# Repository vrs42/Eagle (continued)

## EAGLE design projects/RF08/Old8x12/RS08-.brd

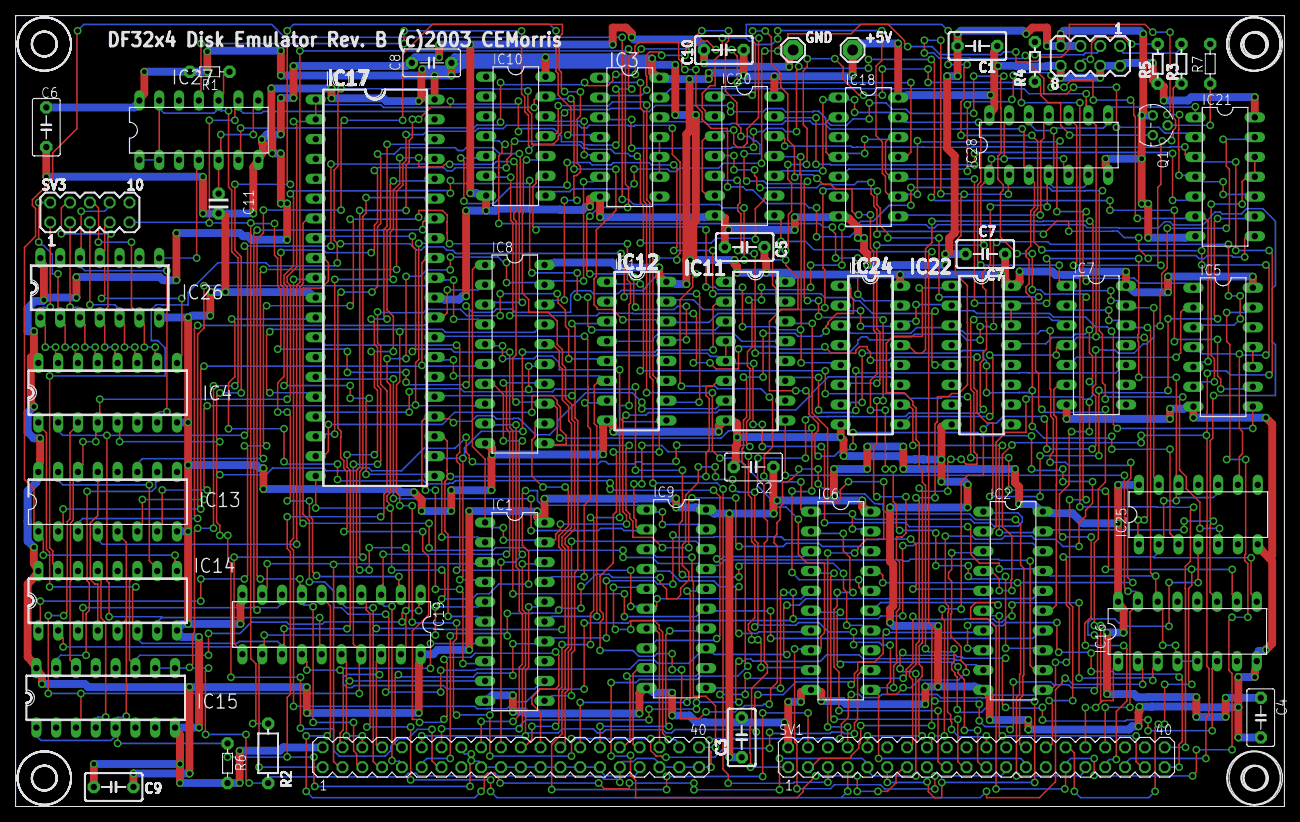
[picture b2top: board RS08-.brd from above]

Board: 2 copper layers, 162.7 x 101.4 mm, 56 parts (0 on the bottom side), 153 nets.

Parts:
+5V: SE14
C1, C2, C3, C4, C5, C6, C7, C8, C9, C10: C5B3.5
C11: C-2,5
GND: SE14
IC1, IC8, IC9, IC19: 74LS240N; DIL20
IC2, IC6: 74LS244N; DIL20
IC3: 74LS00N; DIL14
IC4: 74LS138N; DIL16
IC5: 74LS32N; DIL14
IC7, IC18, IC25: 74LS74N; DIL14
IC10: 74LS04N; DIL14
IC11, IC12, IC13, IC14, IC15, IC16: 74LS191N; DIL16
IC17: DS1258; DIL40
IC20: 74LS02N; DIL14
IC21: 74LS01N; DIL14
IC22, IC24: 74LS155N; DIL16
IC26: 74LS30N; DIL14
IC27: 74LS86N; DIL14
IC28: 74LS07N; DIL14
Q1: 2N3904; TO92
R1: 1K; R-5
R2: 1K; R-7,5
R3, R4, R5: 220; R-5
R6: 0; R-5
R7: 4.7K; R-5
SV1: BUS1; MA20-2
SV2: BUS2; MA20-2
SV3: WRLOCK; MA05-2
SV4: PANEL LEDS; MA04-2
U$1, U$2, U$3, U$4: 3,0

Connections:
0V: IC2.17, IC7.2, IC7.12, IC11.4, IC11.5, IC12.5, IC13.5, IC14.5, IC15.1, IC15.5, IC16.4, IC16.5, IC16.14, R6.1, SV2.16, SV2.17, SV2.19, SV2.21, SV2.23, SV2.25, SV2.27, SV2.29, SV2.33
!660-663: IC5.8, IC22.2, IC24.2, IC24.14
!(NED+EWL): IC2.13, IC20.1
!ACBUS0: IC2.3, IC8.12, SV2.11
!ACBUS1: IC8.14, IC19.3, SV2.9
!ACBUS2: IC8.16, IC19.5, SV2.7
!ACBUS3: IC8.18, IC19.7, SV2.5
!ACBUS4: IC1.3, IC19.9, SV2.3
!ACBUS5: IC1.5, IC19.12, SV2.1
!ACBUS6: IC1.7, IC19.14, SV2.4
!ACBUS7: IC1.9, IC19.16, SV2.6
!ACBUS8: IC1.12, IC19.18, SV2.8
!ACBUS9: IC1.14, IC2.5, SV2.10
!ACBUS10: IC1.16, IC2.7, SV2.12
!ACBUS11: IC1.18, IC2.9, SV2.14
!ACCLEAR: IC21.1, IC28.4, IC28.6, IC28.8, IC28.12, SV1.1
!BADDAC: IC7.3, SV1.10
!BBREAK: IC4.4, IC10.13, IC11.14, IC12.14, IC13.14, IC14.14, IC15.14, IC17.1, IC17.2, SV1.8
!BRK_RQ: IC7.8, SV2.15
!BWCO: IC7.11, IC18.3, SV1.12
!DATA0: IC8.9, SV2.18
!DATA1: IC8.7, SV2.20
!DATA2: IC8.5, SV2.22
!DATA3: IC8.3, SV2.24
!DATA4: IC9.18, SV2.26
!DATA5: IC9.16, SV2.28
!DATA6: IC9.14, SV2.30
!DATA7: IC9.12, SV2.32
!DATA8: IC9.9, SV2.34
!DATA9: IC9.7, SV2.36
!DATA10: IC9.5, SV2.38
!DATA11: IC9.3, SV2.40
!DRL: IC2.15, IC7.6
!EA: IC10.10, SV1.4
!EWL: IC18.8, IC28.11
!INT_RQ: IC21.13, SV1.16
!IOP4: IC10.4, IC24.15
!IOS: IC21.4, IC21.10, IC28.2, SV1.14
!IOT601: IC22.7, IC27.12
!IOT602: IC3.12, IC24.7, IC25.3, IC28.3
!IOT604: IC3.13, IC7.4, IC24.9, IC25.1, IC28.9
!IOT612: IC24.6, IC28.1, IC28.5, IC28.13
!IOT614: IC2.19, IC14.11, IC15.11, IC16.11, IC19.1, IC19.19, IC24.10
!IOT621: IC10.5, IC22.5
!IOT622: IC10.9, IC20.11, IC24.5
!IOT624: IC1.1, IC1.19, IC8.1, IC24.11
!LAD: IC3.8, IC7.10, IC11.11, IC12.11, IC13.11
!OE: IC3.6, IC8.19, IC9.1, IC9.19, IC17.20
!SCL: IC7.1, IC7.13, IC18.1, IC18.13, IC20.10, IC25.13
!WE: IC2.1, IC6.1, IC6.19, IC17.39, IC27.9, R2.2, SV3.9
!WR1: IC4.15, IC26.1, SV3.1
!WR2: IC4.14, IC26.2, SV3.2
!WR3: IC4.13, IC26.3, SV3.3
!WR4: IC4.12, IC26.4, SV3.4
!WR5: IC4.11, IC26.5, SV3.5
!WR6: IC4.10, IC26.6, SV3.6
!WR7: IC4.9, IC26.11, SV3.7
!WR8: IC4.7, IC26.12, SV3.8
BAC0: IC13.9, SV1.18
BAC1: IC13.10, IC15.15, SV1.20
BAC2: IC13.1, IC14.9, SV1.22
BAC3: IC13.15, IC14.10, SV1.24
BAC4: IC12.9, IC14.1, SV1.26
BAC5: IC12.10, IC14.15, SV1.28
BAC6: IC12.1, IC16.10, SV1.30
BAC7: IC12.15, IC16.1, SV1.32
BAC8: IC11.9, IC16.15, SV1.34
BAC9: IC11.10, SV1.36
BAC10: IC11.1, SV1.38
BAC11: IC11.15, SV1.40
BIOP1: IC22.1, SV1.11
BIOP2: IC24.1, SV1.13
BIOP4: IC10.3, SV1.15
BMB0: IC6.2, SV1.17
BMB1: IC6.4, SV1.19
BMB2: IC6.6, SV1.21
BMB3: IC3.1, IC6.8, SV1.23
BMB4: IC3.2, IC6.11, SV1.25
BMB5: IC5.12, IC6.13, SV1.27
BMB6: IC5.13, IC6.15, SV1.29
BMB7: IC6.17, IC22.3, IC24.3, SV1.31
BMB8: IC2.2, IC22.13, IC24.13, SV1.33
BMB9: IC2.4, IC20.12, IC21.3, SV1.35
BMB10: IC2.6, SV1.37
BMB11: IC2.8, SV1.39
BRK_RQ: IC7.9, R7.2
BTS3: IC4.6, SV1.6
DATA_IN: IC3.4, IC4.5, IC25.5, SV2.13
DISK_LED: R4.1, SV4.3
DMA0: IC8.8, IC13.7, IC17.33
DMA1: IC8.6, IC13.6, IC17.32
DMA2: IC8.4, IC13.2, IC17.31
DMA3: IC8.2, IC13.3, IC17.29
DMA4: IC1.17, IC12.7, IC17.28
DMA5: IC1.15, IC12.6, IC17.27
DMA6: IC1.13, IC12.2, IC17.26
DMA7: IC1.11, IC12.3, IC17.25
DMA8: IC1.8, IC11.7, IC17.24
DMA9: IC1.6, IC11.6, IC17.23
DMA10: IC1.4, IC11.2, IC17.22
DMA11: IC1.2, IC11.3, IC17.21
DQ0: IC6.18, IC8.11, IC17.19
DQ1: IC6.16, IC8.13, IC17.18
DQ2: IC6.14, IC8.15, IC17.17
DQ3: IC6.12, IC8.17, IC17.16
DQ4: IC6.9, IC9.2, IC17.15
DQ5: IC6.7, IC9.4, IC17.14
DQ6: IC6.5, IC9.6, IC17.13
DQ7: IC6.3, IC9.8, IC17.12
DQ8: IC2.18, IC9.11, IC17.10
DQ9: IC2.16, IC9.13, IC17.9
DQ10: IC2.14, IC9.15, IC17.8
DQ11: IC2.12, IC9.17, IC17.7
DRL: IC5.2, IC7.5
EA1: IC10.11, IC16.3, IC19.2, SV1.5
EA2: IC16.2, IC19.4, SV1.7
EA3: IC16.6, IC19.6, SV1.9
EMA1: IC14.3, IC17.34, IC19.8
EMA2: IC14.2, IC17.35, IC19.11
EMA3: IC4.1, IC14.6, IC17.36, IC19.13
EMA4: IC4.2, IC14.7, IC17.37, IC19.15
EMA5: IC4.3, IC15.3, IC17.38, IC19.17
EWL: IC5.1, IC18.9, IC20.2
EWLSET: IC18.11, IC27.6
GND: C1.2, C2.2, C3.2, C4.2, C5.2, C6.2, C7.2, C8.2, C9.2, C10.2, C11.2, GND.MP, IC1.10, IC2.10, IC3.7, IC4.8, IC5.7, IC6.10, IC7.7, IC8.10, IC9.10, IC10.7, IC11.8, IC12.8, IC13.8, IC14.8, IC15.8, IC16.8, IC17.11, IC17.30, IC18.7, IC19.10, IC20.7, IC21.7, IC22.8, IC24.8, IC25.7, IC26.7, IC27.7, IC28.7, Q1.3, R6.2, SV1.2, SV2.2, SV4.5, SV4.7
IOT601: IC20.9, IC27.11
IOT621: IC10.6, IC21.9
LAD: IC3.9, IC3.10, IC3.11
unnamed: C11.1, IC27.5, IC27.8
unnamed: IC5.6, IC21.11, IC21.12
unnamed: IC28.10, R3.2
unnamed: IC3.5, IC10.12
unnamed: Q1.1, R4.2
unnamed: R5.2, SV4.6
unnamed: IC13.13, IC14.4
unnamed: IC12.13, IC13.4
unnamed: IC11.13, IC12.4
unnamed: IC3.3, IC5.9
unnamed: IC14.13, IC15.4
unnamed: IC5.10, IC5.11
unnamed: IC20.13, IC21.5
unnamed: IC5.3, IC20.5
unnamed: IC10.8, IC21.2
unnamed: IC26.8, IC27.4
unnamed: Q1.2, R7.1
NED: IC5.4, IC20.3, IC20.6, IC25.9
NEDSET: IC15.2, IC25.11
NOERR: IC20.4, IC21.8
PWRCLR: IC20.8, IC25.4, SV1.3
TRC: IC5.5, IC18.5, IC21.6
V+: IC2.11, IC15.9, IC15.10, IC16.9, IC18.2, IC18.4, IC18.10, IC18.12, IC22.14, IC22.15, IC25.2, IC25.10, IC25.12, IC27.1, IC27.2, IC27.10, IC27.13, R1.1, R2.1, SV2.31, SV2.35, SV2.37, SV2.39
VCC: +5V.MP, C1.1, C2.1, C3.1, C4.1, C5.1, C6.1, C7.1, C8.1, C9.1, C10.1, IC1.20, IC2.20, IC3.14, IC4.16, IC5.14, IC6.20, IC7.14, IC8.20, IC9.20, IC10.14, IC11.16, IC12.16, IC13.16, IC14.16, IC15.16, IC16.16, IC17.40, IC18.14, IC19.20, IC20.14, IC21.14, IC22.16, IC24.16, IC25.14, IC26.14, IC27.14, IC28.14, R1.2, R5.1, SV4.2, SV4.4, SV4.8
WRITELOCK_LED: R3.1, SV4.1

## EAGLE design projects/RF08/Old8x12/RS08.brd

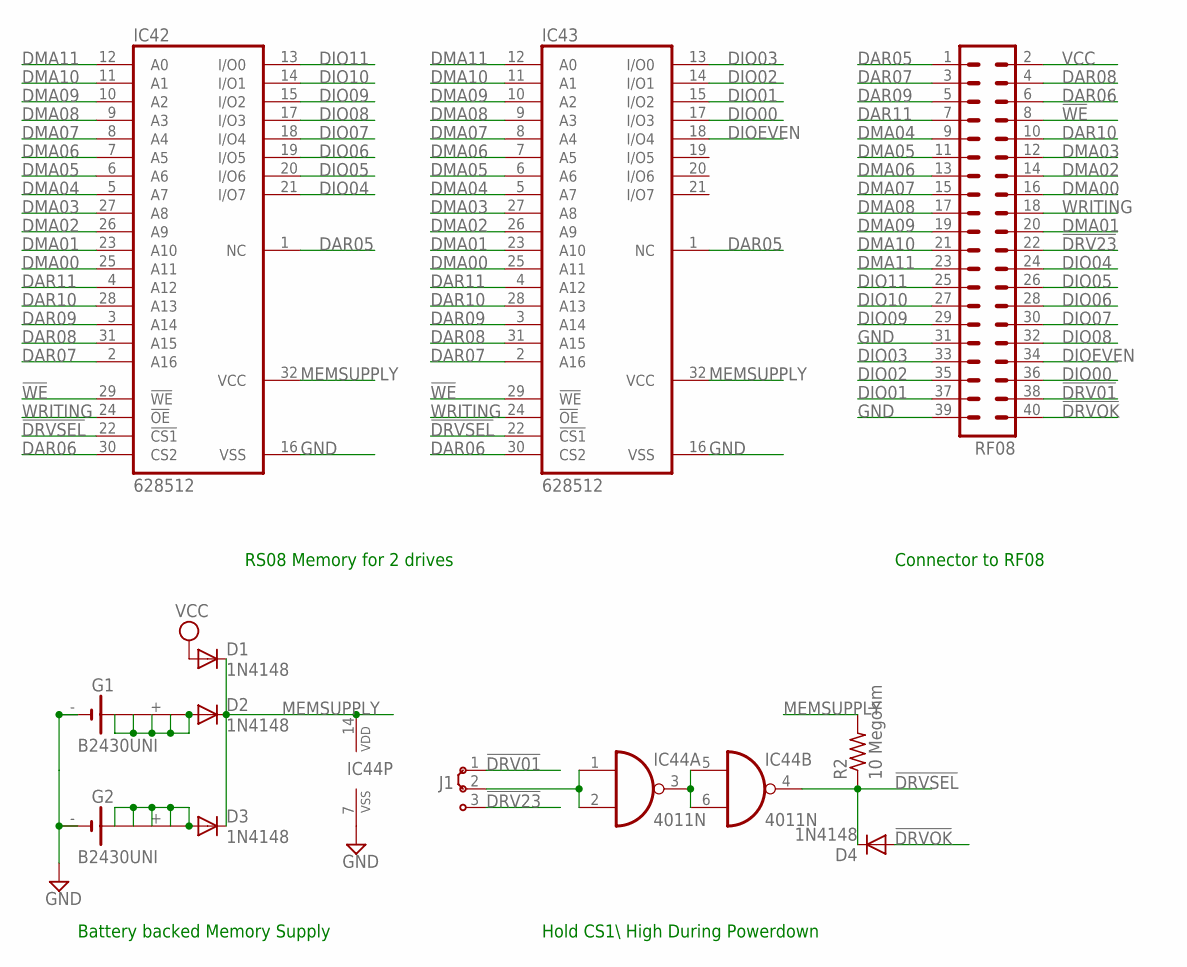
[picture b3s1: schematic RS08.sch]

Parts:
D1, D2, D3, D4: 1N4148; DO35-10
G1, G2: B2430UNI
IC42, IC43: 628512; DIL32
IC44: 4011N; DIL14
J1: J2X2MM; 04C
R2: 10 Megohm; 0207/10
RF08: MA20-2

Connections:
!DRV01: J1.1, RF08.38
!DRV23: J1.3, RF08.22
!DRVOK: D4.A, RF08.40
!DRVSEL: D4.C, IC42.22 (!CS1), IC43.22 (!CS1), IC44.4 (O), R2.1
!WE: IC42.29 (!WE), IC43.29 (!WE), RF08.8
DAR05: IC42.1 (NC), IC43.1 (NC), RF08.1
DAR06: IC42.30 (CS2), IC43.30 (CS2), RF08.6
DAR07: IC42.2 (A16), IC43.2 (A16), RF08.3
DAR08: IC42.31 (A15), IC43.31 (A15), RF08.4
DAR09: IC42.3 (A14), IC43.3 (A14), RF08.5
DAR10: IC42.28 (A13), IC43.28 (A13), RF08.10
DAR11: IC42.4 (A12), IC43.4 (A12), RF08.7
DIO00: IC43.17 (I/O3), RF08.36
DIO01: IC43.15 (I/O2), RF08.37
DIO02: IC43.14 (I/O1), RF08.35
DIO03: IC43.13 (I/O0), RF08.33
DIO04: IC42.21 (I/O7), RF08.24
DIO05: IC42.20 (I/O6), RF08.26
DIO06: IC42.19 (I/O5), RF08.28
DIO07: IC42.18 (I/O4), RF08.30
DIO08: IC42.17 (I/O3), RF08.32
DIO09: IC42.15 (I/O2), RF08.29
DIO10: IC42.14 (I/O1), RF08.27
DIO11: IC42.13 (I/O0), RF08.25
DIOEVEN: IC43.18 (I/O4), RF08.34
DMA00: IC42.25 (A11), IC43.25 (A11), RF08.16
DMA01: IC42.23 (A10), IC43.23 (A10), RF08.20
DMA02: IC42.26 (A9), IC43.26 (A9), RF08.14
DMA03: IC42.27 (A8), IC43.27 (A8), RF08.12
DMA04: IC42.5 (A7), IC43.5 (A7), RF08.9
DMA05: IC42.6 (A6), IC43.6 (A6), RF08.11
DMA06: IC42.7 (A5), IC43.7 (A5), RF08.13
DMA07: IC42.8 (A4), IC43.8 (A4), RF08.15
DMA08: IC42.9 (A3), IC43.9 (A3), RF08.17
DMA09: IC42.10 (A2), IC43.10 (A2), RF08.19
DMA10: IC42.11 (A1), IC43.11 (A1), RF08.21
DMA11: IC42.12 (A0), IC43.12 (A0), RF08.23
GND: G1.-, G1.-@1 (-), G2.-, G2.-@1 (-), IC42.16 (VSS), IC43.16 (VSS), IC44.7 (VSS), RF08.31, RF08.39
MEMSUPPLY: D1.C, D2.C, D3.C, IC42.32 (VCC), IC43.32 (VCC), IC44.14 (VDD), R2.2
unnamed: IC44.3 (O), IC44.5 (I0), IC44.6 (I1)
unnamed: IC44.1 (I0), IC44.2 (I1), J1.2
unnamed: D3.A, G2.+, G2.+@1 (+), G2.+@2 (+), G2.+@3 (+), G2.+@4 (+)
unnamed: D2.A, G1.+, G1.+@1 (+), G1.+@2 (+), G1.+@3 (+), G1.+@4 (+)
VCC: D1.A, RF08.2
WRITING: IC42.24 (!OE), IC43.24 (!OE), RF08.18

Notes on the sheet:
Hold CS1\\ High During Powerdown
Battery backed Memory Supply
RS08 Memory for 2 drives
Connector to RF08

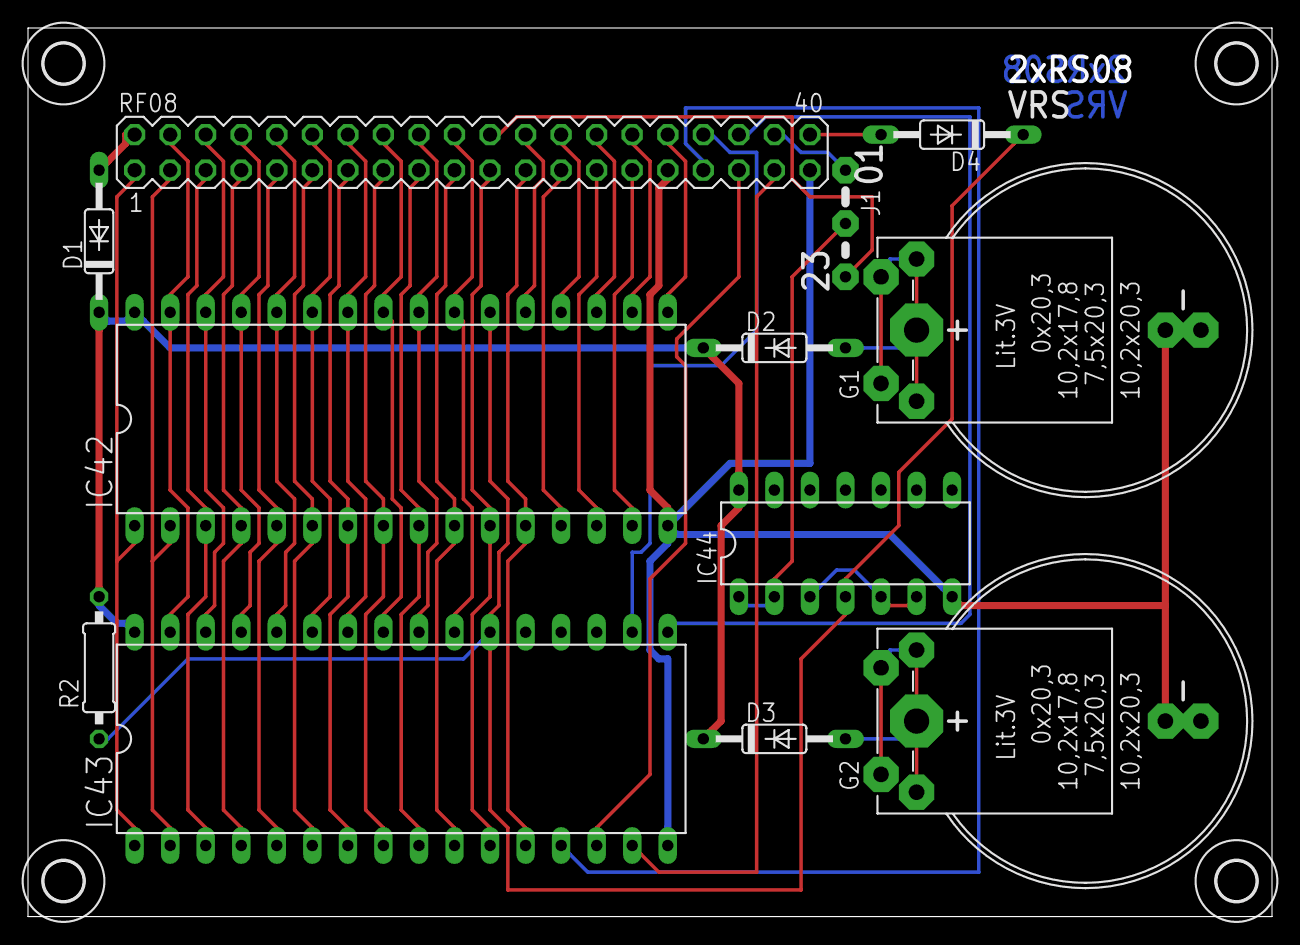
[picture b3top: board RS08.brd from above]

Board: 2 copper layers, 88.9 x 63.5 mm, 16 parts (0 on the bottom side), 45 nets.

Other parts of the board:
U$5, U$6, U$7, U$8: 2,8

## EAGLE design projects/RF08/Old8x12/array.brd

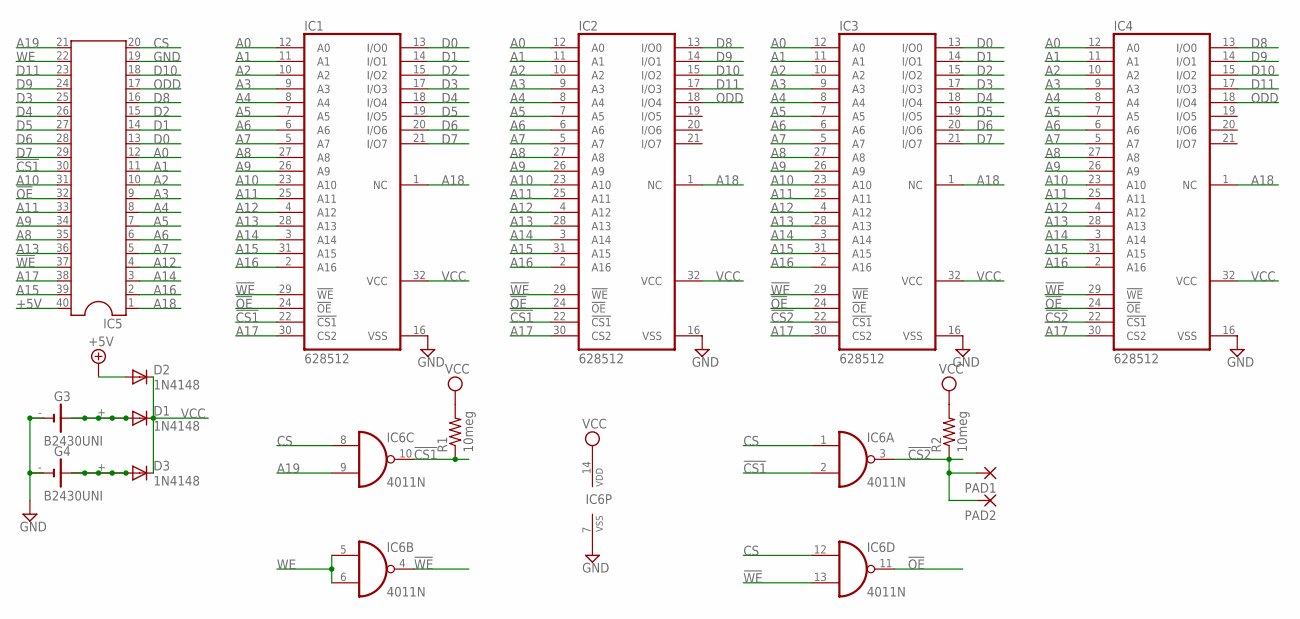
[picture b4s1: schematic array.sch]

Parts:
D1, D2, D3: 1N4148; DO35-10
G3, G4: B2430UNI
IC1, IC2, IC3, IC4: 628512; DIL32
IC5: DIL40
IC6: 4011N; DIL14
PAD1, PAD2: 1,6/0,8
R1, R2: 10meg; 0207/7

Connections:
!CS1: IC1.22 (!CS1), IC2.22 (!CS1), IC5.30, IC6.2 (I1), IC6.10 (O), R1.1
!CS2: IC3.22 (!CS1), IC4.22 (!CS1), IC6.3 (O), PAD1.1, PAD2.1, R2.1
!OE: IC1.24 (!OE), IC2.24 (!OE), IC3.24 (!OE), IC4.24 (!OE), IC5.32, IC6.11 (O)
!WE: IC1.29 (!WE), IC2.29 (!WE), IC3.29 (!WE), IC4.29 (!WE), IC5.37, IC6.4 (O), IC6.13 (I1)
+5V: D2.A, IC5.40
A0: IC1.12 (A0), IC2.12 (A0), IC3.12 (A0), IC4.12 (A0), IC5.12
A1: IC1.11 (A1), IC2.11 (A1), IC3.11 (A1), IC4.11 (A1), IC5.11
A2: IC1.10 (A2), IC2.10 (A2), IC3.10 (A2), IC4.10 (A2), IC5.10
A3: IC1.9 (A3), IC2.9 (A3), IC3.9 (A3), IC4.9 (A3), IC5.9
A4: IC1.8 (A4), IC2.8 (A4), IC3.8 (A4), IC4.8 (A4), IC5.8
A5: IC1.7 (A5), IC2.7 (A5), IC3.7 (A5), IC4.7 (A5), IC5.7
A6: IC1.6 (A6), IC2.6 (A6), IC3.6 (A6), IC4.6 (A6), IC5.6
A7: IC1.5 (A7), IC2.5 (A7), IC3.5 (A7), IC4.5 (A7), IC5.5
A8: IC1.27 (A8), IC2.27 (A8), IC3.27 (A8), IC4.27 (A8), IC5.35
A9: IC1.26 (A9), IC2.26 (A9), IC3.26 (A9), IC4.26 (A9), IC5.34
A10: IC1.23 (A10), IC2.23 (A10), IC3.23 (A10), IC4.23 (A10), IC5.31
A11: IC1.25 (A11), IC2.25 (A11), IC3.25 (A11), IC4.25 (A11), IC5.33
A12: IC1.4 (A12), IC2.4 (A12), IC3.4 (A12), IC4.4 (A12), IC5.4
A13: IC1.28 (A13), IC2.28 (A13), IC3.28 (A13), IC4.28 (A13), IC5.36
A14: IC1.3 (A14), IC2.3 (A14), IC3.3 (A14), IC4.3 (A14), IC5.3
A15: IC1.31 (A15), IC2.31 (A15), IC3.31 (A15), IC4.31 (A15), IC5.39
A16: IC1.2 (A16), IC2.2 (A16), IC3.2 (A16), IC4.2 (A16), IC5.2
A17: IC1.30 (CS2), IC2.30 (CS2), IC3.30 (CS2), IC4.30 (CS2), IC5.38
A18: IC1.1 (NC), IC2.1 (NC), IC3.1 (NC), IC4.1 (NC), IC5.1
A19: IC5.21, IC6.9 (I1)
CS: IC5.20, IC6.1 (I0), IC6.8 (I0), IC6.12 (I0)
D0: IC1.13 (I/O0), IC3.13 (I/O0), IC5.13
D1: IC1.14 (I/O1), IC3.14 (I/O1), IC5.14
D2: IC1.15 (I/O2), IC3.15 (I/O2), IC5.15
D3: IC1.17 (I/O3), IC3.17 (I/O3), IC5.25
D4: IC1.18 (I/O4), IC3.18 (I/O4), IC5.26
D5: IC1.19 (I/O5), IC3.19 (I/O5), IC5.27
D6: IC1.20 (I/O6), IC3.20 (I/O6), IC5.28
D7: IC1.21 (I/O7), IC3.21 (I/O7), IC5.29
D8: IC2.13 (I/O0), IC4.13 (I/O0), IC5.16
D9: IC2.14 (I/O1), IC4.14 (I/O1), IC5.24
D10: IC2.15 (I/O2), IC4.15 (I/O2), IC5.18
D11: IC2.17 (I/O3), IC4.17 (I/O3), IC5.23
GND: G3.-, G3.-@1 (-), G4.-, G4.-@1 (-), IC1.16 (VSS), IC2.16 (VSS), IC3.16 (VSS), IC4.16 (VSS), IC5.19, IC6.7 (VSS)
unnamed: D1.A, G3.+, G3.+@1 (+), G3.+@2 (+), G3.+@3 (+), G3.+@4 (+)
unnamed: D3.A, G4.+, G4.+@1 (+), G4.+@2 (+), G4.+@3 (+), G4.+@4 (+)
ODD: IC2.18 (I/O4), IC4.18 (I/O4), IC5.17
VCC: D1.C, D2.C, D3.C, IC1.32 (VCC), IC2.32 (VCC), IC3.32 (VCC), IC4.32 (VCC), IC6.14 (VDD), R1.2, R2.2
WE: IC5.22, IC6.5 (I0), IC6.6 (I1)

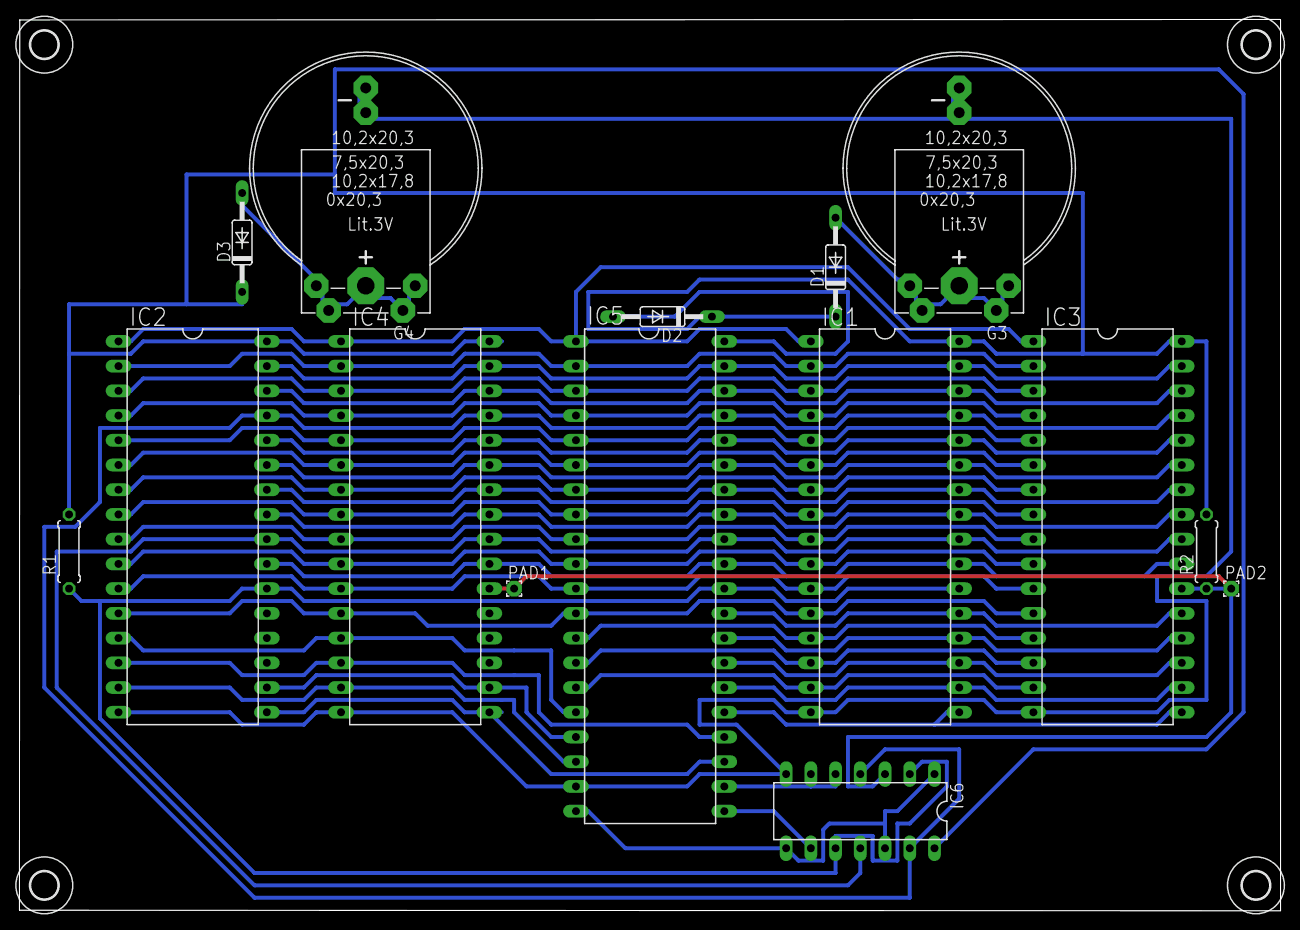
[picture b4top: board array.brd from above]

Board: 2 copper layers, 129.5 x 91.6 mm, 19 parts (0 on the bottom side), 44 nets.

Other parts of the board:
U$1, U$2, U$3, U$4: 2,8

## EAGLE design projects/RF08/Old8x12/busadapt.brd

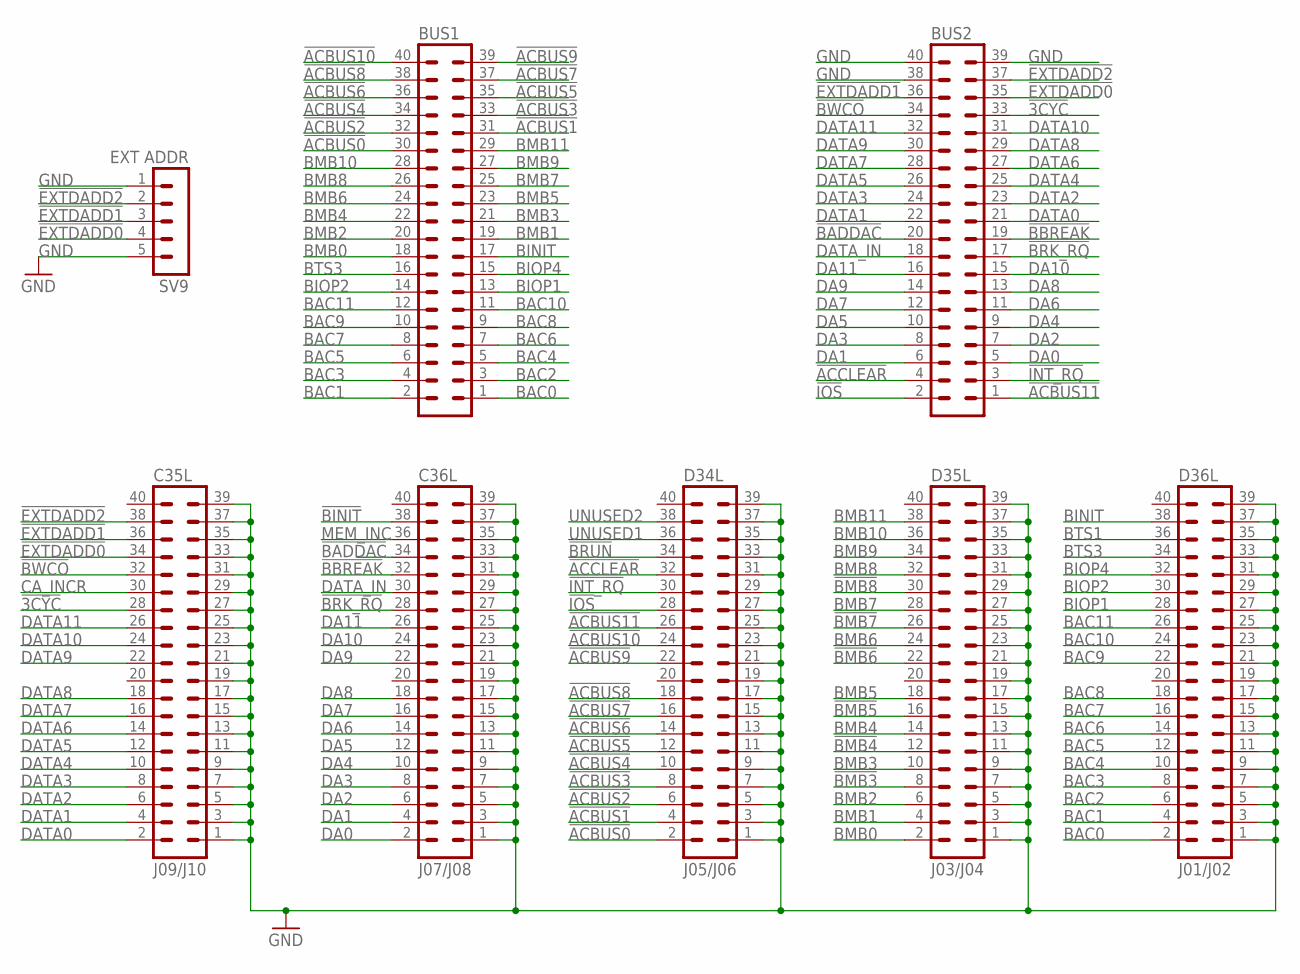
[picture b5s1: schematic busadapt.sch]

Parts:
BUS1, BUS2: MA20-2
C35L: J09/J10; MA20-2
C36L: J07/J08; MA20-2
D34L: J05/J06; MA20-2
D35L: J03/J04; MA20-2
D36L: J01/J02; MA20-2
SV9: EXT ADDR; MA05-1

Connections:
!3CYC: BUS2.33, C35L.28
!ACBUS0: BUS1.30, D34L.2
!ACBUS1: BUS1.31, D34L.4
!ACBUS2: BUS1.32, D34L.6
!ACBUS3: BUS1.33, D34L.8
!ACBUS4: BUS1.34, D34L.10
!ACBUS5: BUS1.35, D34L.12
!ACBUS6: BUS1.36, D34L.14
!ACBUS7: BUS1.37, D34L.16
!ACBUS8: BUS1.38, D34L.18
!ACBUS9: BUS1.39, D34L.22
!ACBUS10: BUS1.40, D34L.24
!ACBUS11: BUS2.1, D34L.26
!ACCLEAR: BUS2.4, D34L.32
!BADDAC: BUS2.20, C36L.34
!BBREAK: BUS2.19, C36L.32
!BINIT: C36L.38
!BMB3: D35L.8
!BMB4: D35L.12
!BMB5: D35L.16
!BMB6: D35L.22
!BMB7: D35L.26
!BMB8: D35L.30
!BRK_RQ: BUS2.17, C36L.28
!BRUN: D34L.34
!BWCO: BUS2.34, C35L.32
!EXTDADD0: BUS2.35, C35L.34, SV9.4
!EXTDADD1: BUS2.36, C35L.36, SV9.3
!EXTDADD2: BUS2.37, C35L.38, SV9.2
!INT_RQ: BUS2.3, D34L.30
!IOS: BUS2.2, D34L.28
BAC0: BUS1.1, D36L.2
BAC1: BUS1.2, D36L.4
BAC2: BUS1.3, D36L.6
BAC3: BUS1.4, D36L.8
BAC4: BUS1.5, D36L.10
BAC5: BUS1.6, D36L.12
BAC6: BUS1.7, D36L.14
BAC7: BUS1.8, D36L.16
BAC8: BUS1.9, D36L.18
BAC9: BUS1.10, D36L.22
BAC10: BUS1.11, D36L.24
BAC11: BUS1.12, D36L.26
BINIT: BUS1.17, D36L.38
BIOP1: BUS1.13, D36L.28
BIOP2: BUS1.14, D36L.30
BIOP4: BUS1.15, D36L.32
BMB0: BUS1.18, D35L.2
BMB1: BUS1.19, D35L.4
BMB2: BUS1.20, D35L.6
BMB3: BUS1.21, D35L.10
BMB4: BUS1.22, D35L.14
BMB5: BUS1.23, D35L.18
BMB6: BUS1.24, D35L.24
BMB7: BUS1.25, D35L.28
BMB8: BUS1.26, D35L.32
BMB9: BUS1.27, D35L.34
BMB10: BUS1.28, D35L.36
BMB11: BUS1.29, D35L.38
BTS1: D36L.36
BTS3: BUS1.16, D36L.34
CA_INCR: C35L.30
DA0: BUS2.5, C36L.2
DA1: BUS2.6, C36L.4
DA2: BUS2.7, C36L.6
DA3: BUS2.8, C36L.8
DA4: BUS2.9, C36L.10
DA5: BUS2.10, C36L.12
DA6: BUS2.11, C36L.14
DA7: BUS2.12, C36L.16
DA8: BUS2.13, C36L.18
DA9: BUS2.14, C36L.22
DA10: BUS2.15, C36L.24
DA11: BUS2.16, C36L.26
DATA0: BUS2.21, C35L.2
DATA1: BUS2.22, C35L.4
DATA2: BUS2.23, C35L.6
DATA3: BUS2.24, C35L.8
DATA4: BUS2.25, C35L.10
DATA5: BUS2.26, C35L.12
DATA6: BUS2.27, C35L.14
DATA7: BUS2.28, C35L.16
DATA8: BUS2.29, C35L.18
DATA9: BUS2.30, C35L.22
DATA10: BUS2.31, C35L.24
DATA11: BUS2.32, C35L.26
DATA_IN: BUS2.18, C36L.30
GND: BUS2.38, BUS2.39, BUS2.40, C35L.1, C35L.3, C35L.5, C35L.7, C35L.9, C35L.11, C35L.13, C35L.15, C35L.17, C35L.19, C35L.21, C35L.23, C35L.25, C35L.27, C35L.29, C35L.31, C35L.33, C35L.35, C35L.37, C35L.39, C36L.1, C36L.3, C36L.5, C36L.7, C36L.9, C36L.11, C36L.13, C36L.15, C36L.17, C36L.19, C36L.21, C36L.23, C36L.25, C36L.27, C36L.29, C36L.31, C36L.33, C36L.35, C36L.37, C36L.39, D34L.1, D34L.3, D34L.5, D34L.7, D34L.9, D34L.11, D34L.13, D34L.15, D34L.17, D34L.19, D34L.21, D34L.23, D34L.25, D34L.27, D34L.29, D34L.31, D34L.33, D34L.35, D34L.37, D34L.39, D35L.1, D35L.3, D35L.5, D35L.7, D35L.9, D35L.11, D35L.13, D35L.15, D35L.17, D35L.19, D35L.21, D35L.23, D35L.25, D35L.27, D35L.29, D35L.31, D35L.33, D35L.35, D35L.37, D35L.39, D36L.1, D36L.3, D36L.5, D36L.7, D36L.9, D36L.11, D36L.13, D36L.15, D36L.17, D36L.19, D36L.21, D36L.23, D36L.25, D36L.27, D36L.29, D36L.31, D36L.33, D36L.35, D36L.37, D36L.39, SV9.1, SV9.5
MEM_INC: C36L.36
UNUSED1: D34L.36
UNUSED2: D34L.38

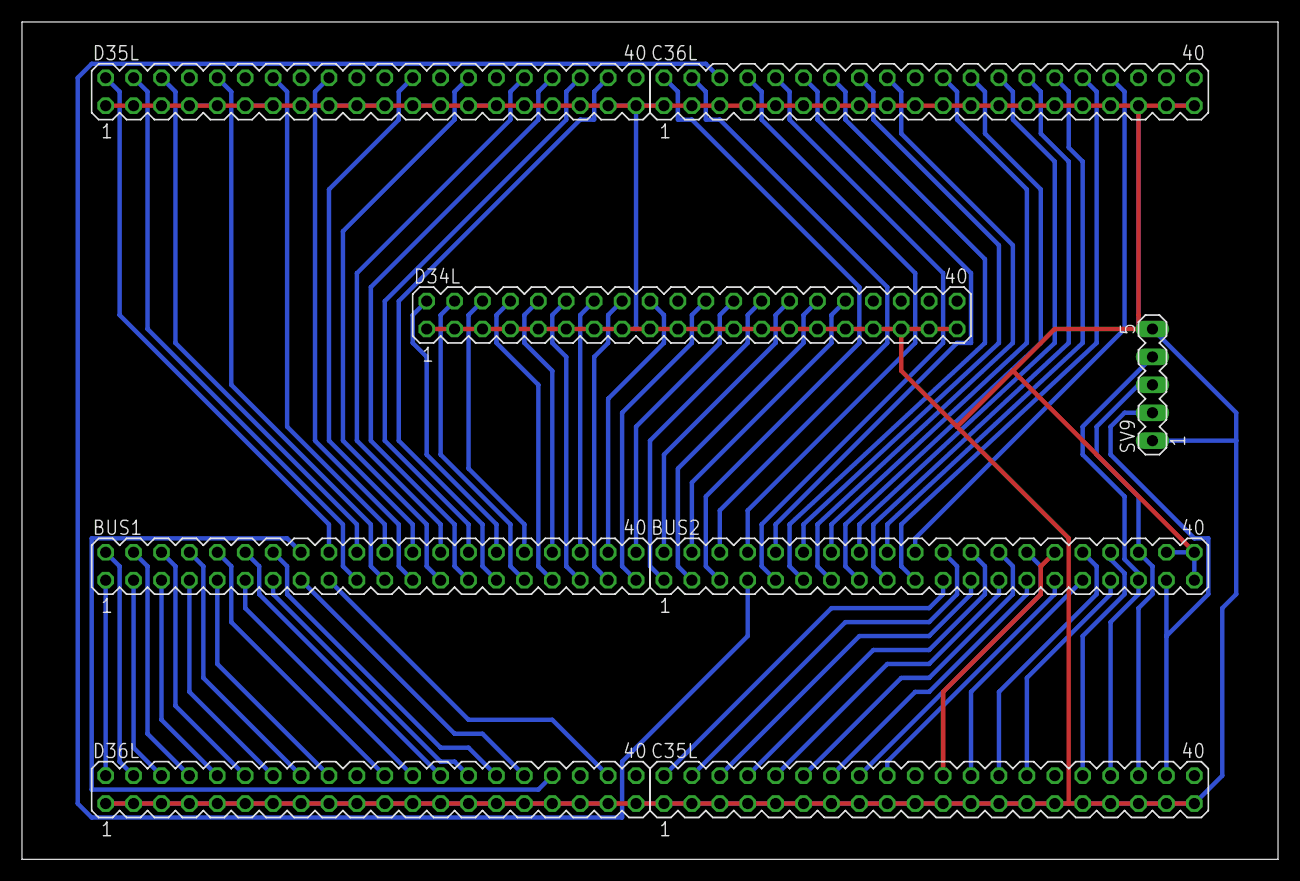
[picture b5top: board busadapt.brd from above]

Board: 2 copper layers, 114.3 x 76.2 mm, 8 parts (0 on the bottom side), 78 nets.
